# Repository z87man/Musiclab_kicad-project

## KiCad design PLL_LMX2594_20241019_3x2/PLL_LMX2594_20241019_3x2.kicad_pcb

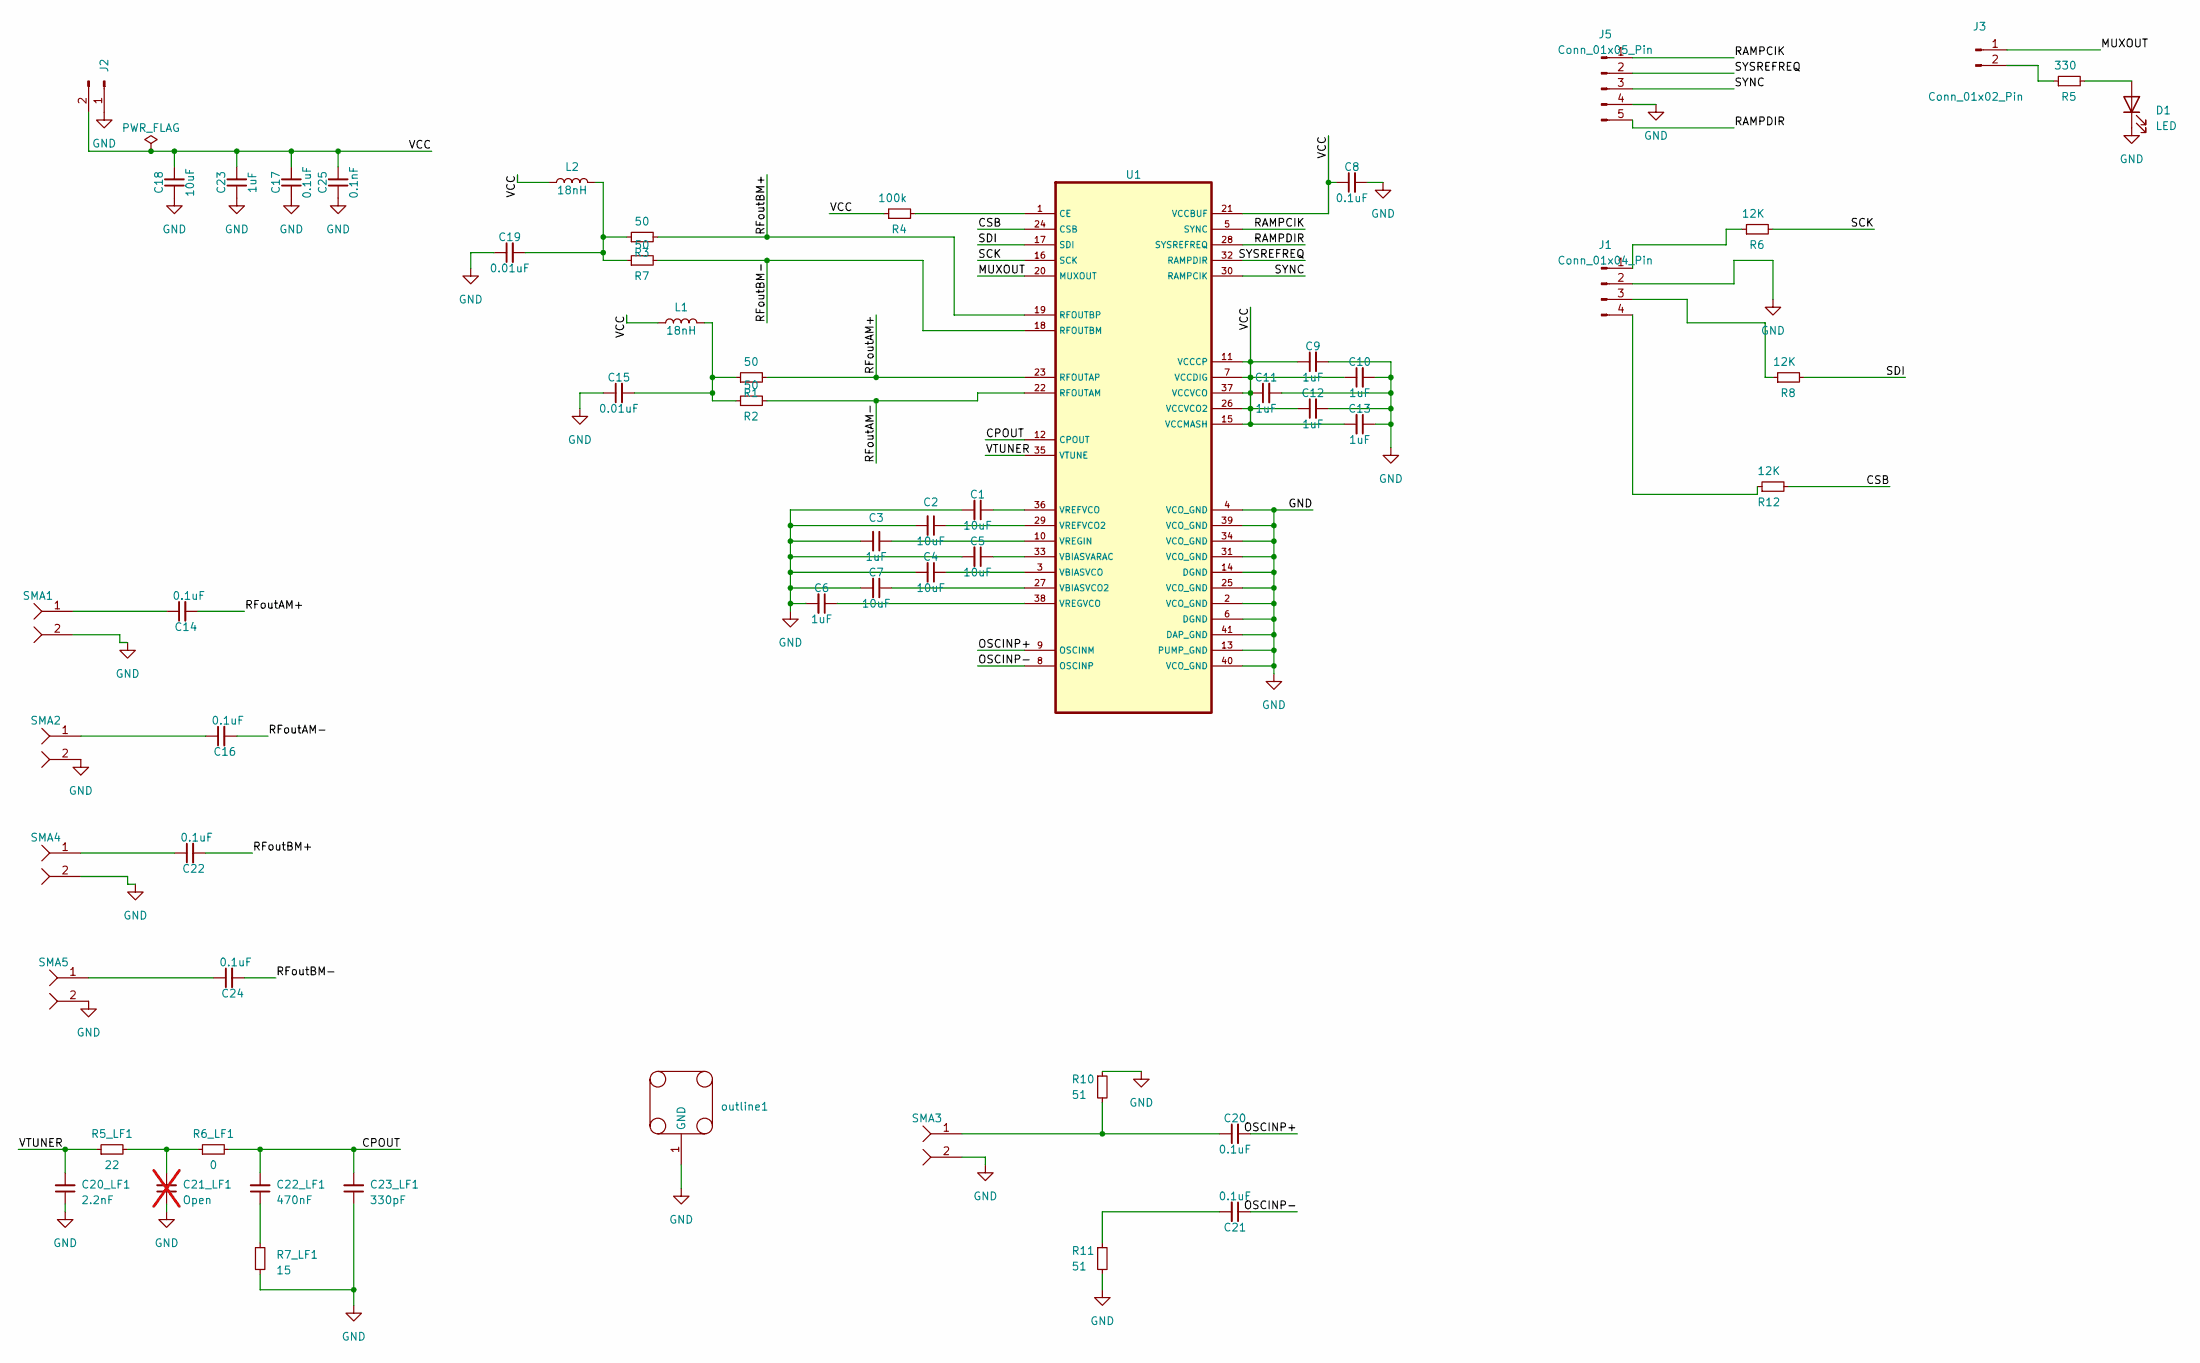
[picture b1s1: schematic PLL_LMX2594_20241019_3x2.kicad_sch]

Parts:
C1, C2, C4, C5, C7, C18: 10uF; C_0603_1608Metric
C3, C6, C9, C10, C11, C12, C13, C23: 1uF; C_0402_1005Metric
C8, C14, C16, C17, C20, C21, C22, C24: 0.1uF; C_0402_1005Metric
C15, C19: 0.01uF; C_0402_1005Metric
C20_LF1: 2.2nF; C_0402_1005Metric
C21_LF1: Open; C_0402_1005Metric; not fitted
C22_LF1: 470nF; C_0402_1005Metric
C23_LF1: 330pF; C_0402_1005Metric
C25: 0.1nF; C_0402_1005Metric
D1: LED; LED_0603_1608Metric
J1: Conn_01x04_Pin; JST_XH_B4B-XH-A_1x04_P2.50mm_Vertical
J2: Conn_01x02_Pin; JST_XH_B2B-XH-A_1x02_P2.50mm_Vertical
J3: Conn_01x02_Pin; PinHeader_1x02_P2.54mm_Vertical
J5: Conn_01x05_Pin; JST_XH_B5B-XH-A_1x05_P2.50mm_Vertical
L1, L2: 18nH; L_0603_1608Metric
R1, R2, R3, R7: 50; R_0402_1005Metric
R4: 100k; R_0402_1005Metric
R5: 330; R_0402_1005Metric
R5_LF1: 22; R_0402_1005Metric
R6, R8, R12: 12K; R_0402_1005Metric
R6_LF1: 0; R_0402_1005Metric
R7_LF1: 15; R_0402_1005Metric
R10, R11: 51; R_0402_1005Metric
SMA1, SMA2, SMA3, SMA4, SMA5: SMA_KHD_Back
U1: LMX2594-QFN41N
outline1: Outline_4x3_cavity_20230728

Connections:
/CPOUT: C22_LF1.2, C23_LF1.2, R6_LF1.2, U1.12 (CPOUT)
/MUXOUT: J3.1, U1.20 (MUXOUT)
/OSCINP+: C20.2, U1.9 (OSCINM)
/OSCINP-: C21.1, U1.8 (OSCINP)
/RAMPCIK: J5.1, U1.5 (SYNC); also elsewhere on the board
/RAMPDIR: J5.5, U1.28 (SYSREFREQ); also elsewhere on the board
/RFoutAM+: C14.2, R1.2, U1.23 (RFOUTAP)
/RFoutAM-: C16.2, R2.2, U1.22 (RFOUTAM)
/RFoutBM+: C22.2, R3.2, U1.19 (RFOUTBP)
/RFoutBM-: C24.2, R7.2, U1.18 (RFOUTBM)
/SDI: R8.2, U1.17 (SDI)
/SYNC: J5.3, U1.30 (RAMPCIK); also elsewhere on the board
/SYSREFREQ: J5.2, U1.32 (RAMPDIR); also elsewhere on the board
/VCC: C8.1, C9.1, C10.1, C11.1, C12.1, C13.2, C17.2, C18.2, C23.2, C25.2, J2.2, L1.1, L2.1, R4.1, U1.7 (VCCDIG), U1.11 (VCCCP), U1.15 (VCCMASH), U1.21 (VCCBUF), U1.26 (VCCVCO2), U1.37 (VCCVCO)
/VTUNER: C20_LF1.2, R5_LF1.1, U1.35 (VTUNE)
GND: C1.2, C2.2, C3.2, C4.2, C5.2, C6.2, C7.2, C8.2, C9.2, C10.2, C11.2, C12.2, C13.1, C15.1, C17.1, C18.1, C19.1, C20_LF1.1, C21_LF1.1, C23.1, C23_LF1.1, C25.1, D1.1 (K), J1.2, J2.1, J5.4, R7_LF1.2, R10.1, R11.2, SMA1.2, SMA2.2, SMA3.2, SMA4.2, SMA5.2, U1.2 (VCO_GND), U1.4 (VCO_GND), U1.6 (DGND), U1.13 (PUMP_GND), U1.14 (DGND), U1.25 (VCO_GND), U1.31 (VCO_GND), U1.34 (VCO_GND), U1.39 (VCO_GND), U1.40 (VCO_GND), U1.41 (DAP_GND), outline1.1 (GND); also elsewhere on the board
unnamed: C14.1, SMA1.1
unnamed: C15.2, L1.2, R1.1, R2.1
unnamed: C16.1, SMA2.1
unnamed: C19.2, L2.2, R3.1, R7.1
unnamed: C20.1, R10.2, SMA3.1
unnamed: C21.2, R11.1
unnamed: C21_LF1.2, R5_LF1.2, R6_LF1.1
unnamed: C22.1, SMA4.1
unnamed: C22_LF1.1, R7_LF1.1
unnamed: C24.1, SMA5.1
unnamed: D1.2 (A), R5.2
unnamed: J1.1, R6.1
unnamed: J1.3, R8.1
unnamed: J1.4, R12.1
unnamed: J3.2, R5.1
unnamed: R4.2, U1.1 (CE)
unnamed: C5.1, U1.33 (VBIASVARAC)
unnamed: C7.1, U1.27 (VBIASVCO2)
unnamed: C4.1, U1.3 (VBIASVCO)
unnamed: C2.1, U1.29 (VREFVCO2)
unnamed: C1.1, U1.36 (VREFVCO)
unnamed: C3.1, U1.10 (VREGIN)
unnamed: C6.1, U1.38 (VREGVCO)

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
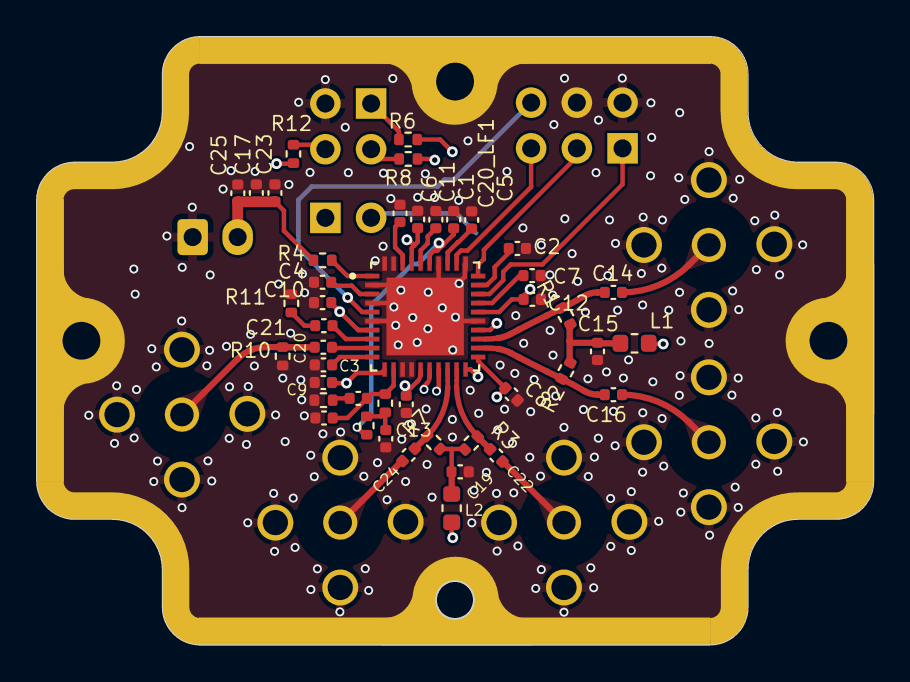
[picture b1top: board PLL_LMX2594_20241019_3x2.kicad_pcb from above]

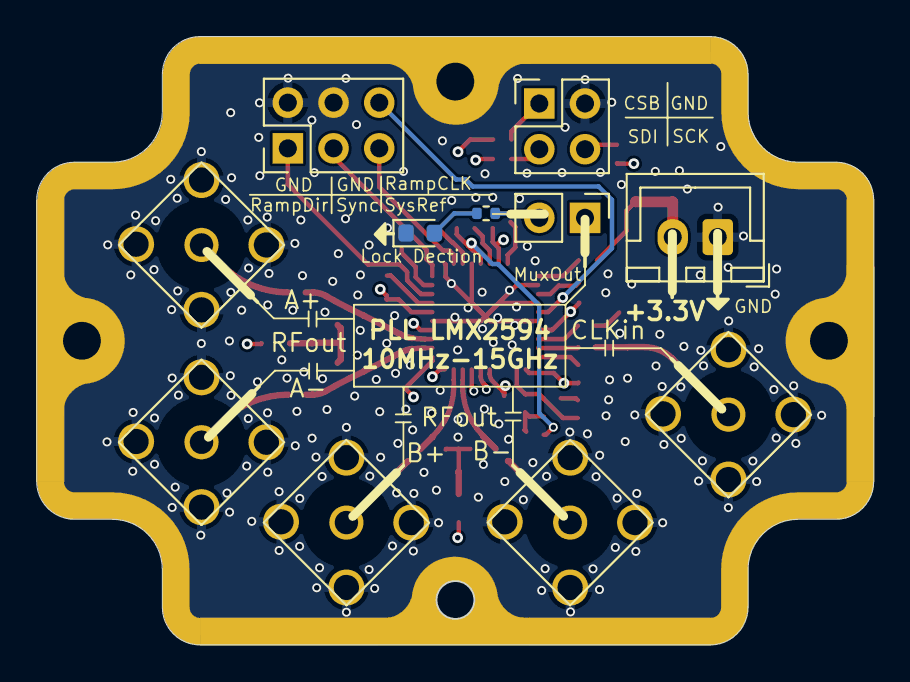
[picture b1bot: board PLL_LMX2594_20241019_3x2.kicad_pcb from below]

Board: 4 copper layers, 46.5 x 33.8 mm, 56 parts (11 on the bottom side), 41 nets.

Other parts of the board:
J4: Conn_01x06_Pin; PinHeader_2x03_P2.54mm_Vertical

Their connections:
/RAMPCIK: J4.6; also elsewhere on the board
/RAMPDIR: J4.1; also elsewhere on the board
/SYNC: J4.3; also elsewhere on the board
/SYSREFREQ: J4.5; also elsewhere on the board
GND: J4.2, J4.4; also elsewhere on the board

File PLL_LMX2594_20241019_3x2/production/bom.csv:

Designator,Footprint,Quantity,Value,LCSC Part #
"C1, C2, C4, C5, C7",0402,5,10uF,
"C10, C11, C12, C13, C23, C3, C6, C9",0402,8,1uF,
"C14, C16, C17, C20, C21, C22, C24, C8",0402,8,0.1uF,
"C15, C19",0402,2,0.01uF,
C20_LF1,0402,1,2.2nF,
C21_LF1,0402,1,Open,
C22_LF1,0402,1,470nF,
C23_LF1,0402,1,330pF,
C25,0402,1,0.1nF,
D1,0603,1,LED,
J1,PinHeader_2x02_P2.54mm_Vertical,1,Conn_01x04_Pin,
J2,JST_XH_B2B-XH-A_1x02_P2.50mm_Vertical,1,Conn_01x02_Pin,
J3,PinHeader_1x02_P2.54mm_Vertical,1,Conn_01x02_Pin,
J4,PinHeader_2x03_P2.54mm_Vertical,1,Conn_01x06_Pin,
"L1, L2",0603,2,18nH,
"R1, R2, R3, R7",0402,4,50,
"R10, R11",0402,2,51,
"R12, R6, R8",0402,3,12K,
R4,0402,1,100k,
R5,0402,1,330,
R5_LF1,0402,1,22,
R6_LF1,0402,1,0,
R7_LF1,0402,1,15,
"SMA1, SMA2, SMA3, SMA4, SMA5",SMA_KHD_Back,5,~,
U1,LMX2594-QFN41N,1,~,
outline1,Outline_3x2_cavity_1.5mm,1,~,

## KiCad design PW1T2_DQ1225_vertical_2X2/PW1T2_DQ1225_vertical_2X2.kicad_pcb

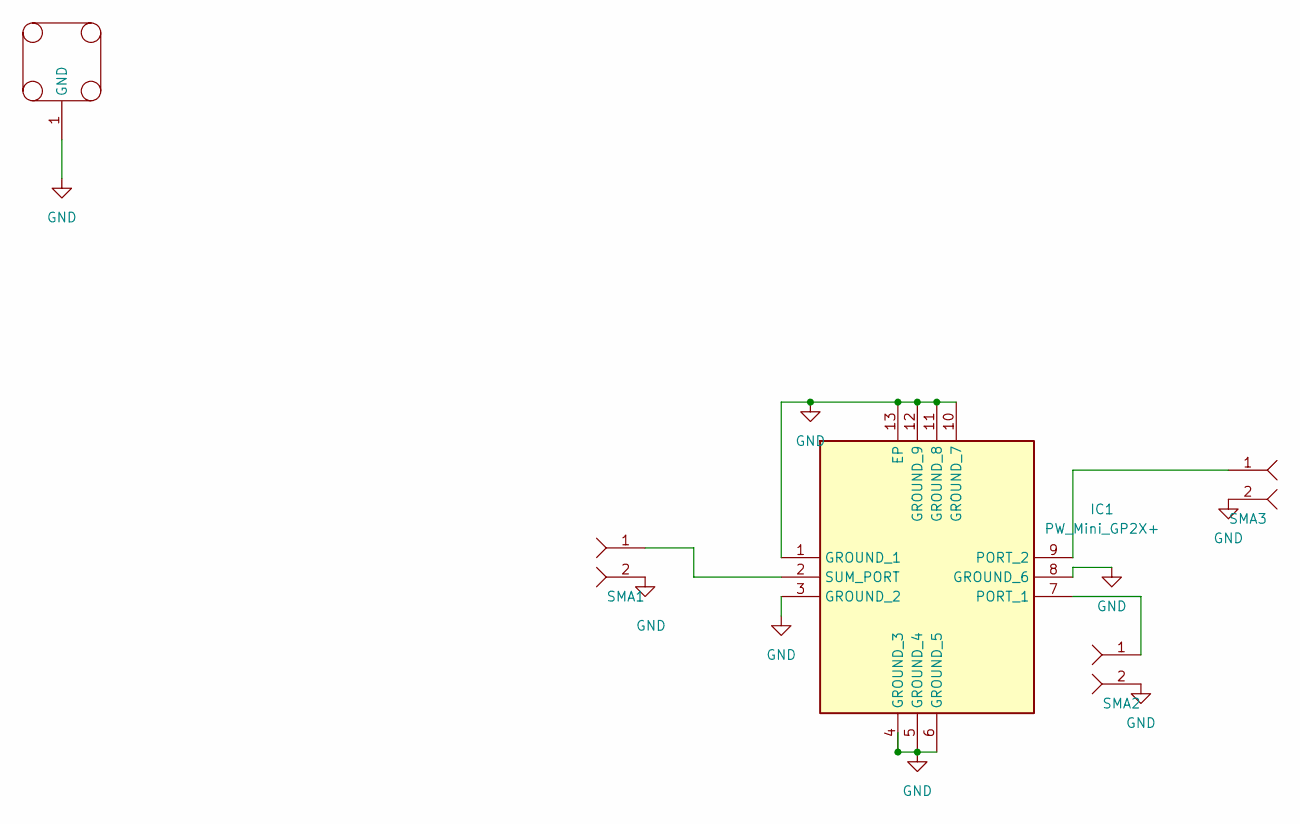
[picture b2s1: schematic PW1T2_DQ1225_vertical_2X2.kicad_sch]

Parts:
IC1: PW_Mini_GP2X+; PW_MINI_1T2_DQ1225_QFN51P300X300X89-13N; Mouser Part Number 139-GP2X
SMA1, SMA2, SMA3: SMA_KHD_Back
outline1: Outline_2x2_cavity_20231207

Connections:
GND: IC1.1 (GROUND_1), IC1.3 (GROUND_2), IC1.4 (GROUND_3), IC1.5 (GROUND_4), IC1.6 (GROUND_5), IC1.8 (GROUND_6), IC1.10 (GROUND_7), IC1.11 (GROUND_8), IC1.12 (GROUND_9), IC1.13 (EP), SMA1.2, SMA2.2, SMA3.2, outline1.1 (GND)
unnamed: IC1.7 (PORT_1), SMA2.1
unnamed: IC1.9 (PORT_2), SMA3.1
unnamed: IC1.2 (SUM_PORT), SMA1.1

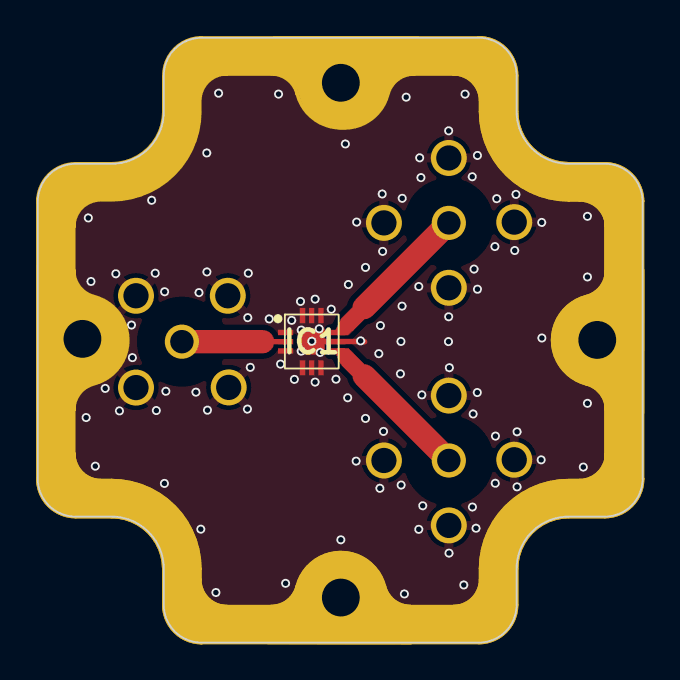
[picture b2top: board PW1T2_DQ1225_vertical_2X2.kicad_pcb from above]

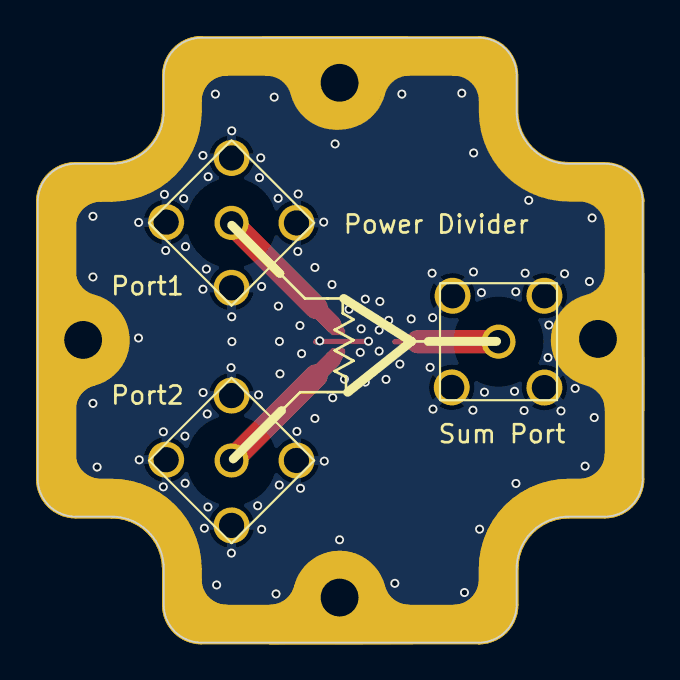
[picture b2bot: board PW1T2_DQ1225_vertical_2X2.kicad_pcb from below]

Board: 2 copper layers, 33.6 x 33.6 mm, 5 parts (3 on the bottom side), 4 nets.

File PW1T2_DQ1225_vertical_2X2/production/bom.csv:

Designator,Footprint,Quantity,Value,LCSC Part #
IC1,PW_MINI_1T2_DQ1225_QFN51P300X300X89-13N,1,PW_Mini_GP2X+,
"SMA1, SMA2, SMA3",SMA_KHD_Back,3,~,
outline1,Outline_2x2_cavity_20231207,1,~,

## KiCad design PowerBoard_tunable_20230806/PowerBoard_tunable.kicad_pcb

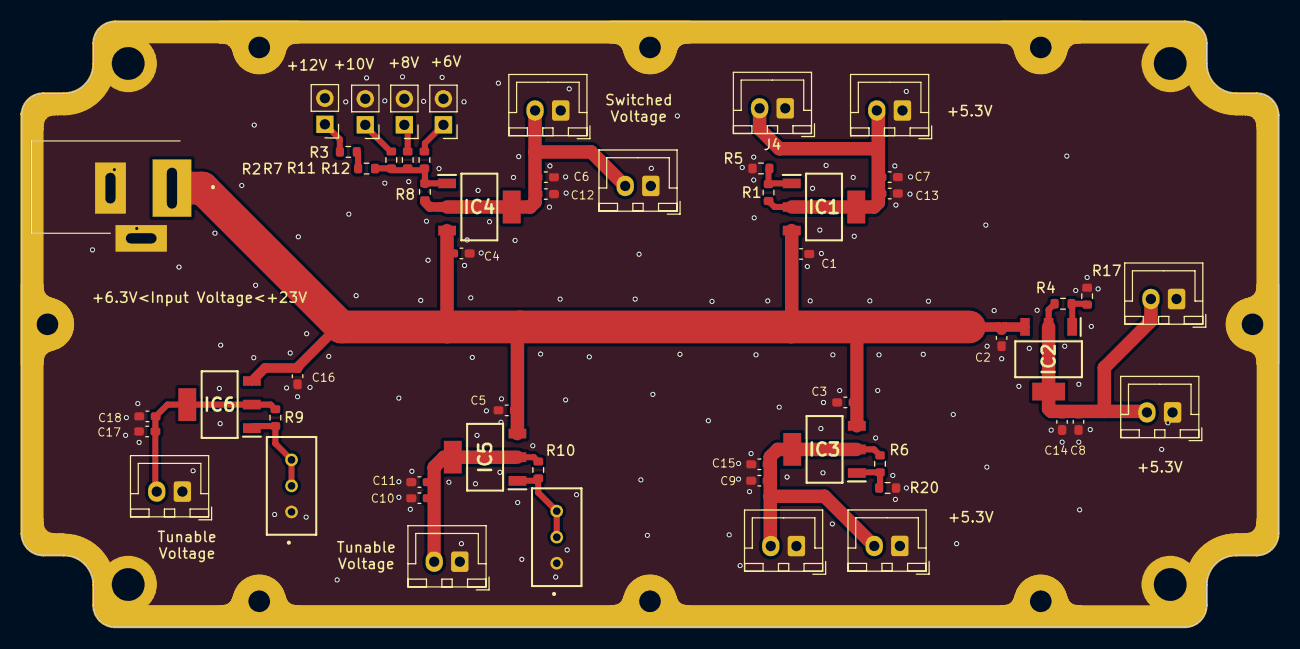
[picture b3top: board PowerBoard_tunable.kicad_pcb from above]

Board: 2 copper layers, 122.5 x 59.0 mm, 56 parts (0 on the bottom side), 19 nets.

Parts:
C1, C2, C3, C4, C5, C6, C7, C8, C9, C10, C16, C17: 0.1uF; C_0603_1608Metric_0603 usual
C11, C12, C13, C14, C15, C18: 4.7uF; C_0603_1608Metric_0603 usual
IC1, IC2, IC3, IC4, IC5, IC6: DC_LM317DCYR; DC_LM317_SOT230P700X180-4N
J1, J12, J13, J14: Conn_01x02_Pin; PinHeader_1x02_P2.54mm_Vertical
J2, J3, J4, J5, J6, J7, J8, J10, J11, J15: Conn_01x02_Pin; JST_XH_B2B-XH-A_1x02_P2.50mm_Vertical
J9: DC_Socket_4840.2211; DC_Socket_48402211
R1, R4, R6, R8, R9, R10: 1k; R_0603_1608Metric
R2, R5, R17, R20: 3.3k; R_0603_1608Metric
R3, R11: 5.6k; R_0603_1608Metric
R7: 7k; R_0603_1608Metric
R12: 3.9k; R_0603_1608Metric
VR1, VR2: Resistor_3296W-1-104LF; Resistor_3296W-1
outline1: Outline_9x4_cavity_20230711

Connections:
GND: C1.2, C2.2, C3.2, C4.2, C5.2, C6.2, C7.2, C8.2, C9.2, C10.2, C11.2, C12.2, C13.2, C14.2, C15.2, C16.2, C17.2, C18.2, J1.2, J2.1, J3.1, J4.1, J5.1, J6.1, J7.1, J8.1, J9.2, J9.3, J10.1, J11.1, J12.2, J13.2, J14.2, J15.1, R5.1, R17.1, R20.1, VR1.1 (CCW), VR2.1 (CCW), outline1.1 (GND)
unnamed: IC1.1 (ADJUST), R1.2, R5.2
unnamed: C7.1, C13.1, IC1.2 (OUTPUT_1), IC1.4 (OUTPUT_2), J2.2, J4.2, R1.1
unnamed: IC2.1 (ADJUST), R4.2, R17.2
unnamed: C8.1, C14.1, IC2.2 (OUTPUT_1), IC2.4 (OUTPUT_2), J3.2, J6.2, R4.1
unnamed: IC3.1 (ADJUST), R6.2, R20.2
unnamed: C9.1, C15.1, IC3.2 (OUTPUT_1), IC3.4 (OUTPUT_2), J5.2, J8.2, R6.1
unnamed: IC4.1 (ADJUST), R2.2, R7.2, R8.2, R11.2, R12.2
unnamed: C6.1, C12.1, IC4.2 (OUTPUT_1), IC4.4 (OUTPUT_2), J7.2, J15.2, R8.1
unnamed: IC5.1 (ADJUST), R10.2, VR1.2 (WIPER), VR1.3 (CW)
unnamed: C10.1, C11.1, IC5.2 (OUTPUT_1), IC5.4 (OUTPUT_2), J11.2, R10.1
unnamed: IC6.1 (ADJUST), R9.2, VR2.2 (WIPER), VR2.3 (CW)
unnamed: C17.1, C18.1, IC6.2 (OUTPUT_1), IC6.4 (OUTPUT_2), J10.2, R9.1
unnamed: J1.1, R3.1
unnamed: J12.1, R11.1
unnamed: J13.1, R7.1
unnamed: J14.1, R12.1
unnamed: R2.1, R3.2
input: C1.1, C2.1, C3.1, C4.1, C5.1, C16.1, IC1.3 (INPUT), IC2.3 (INPUT), IC3.3 (INPUT), IC4.3 (INPUT), IC5.3 (INPUT), IC6.3 (INPUT), J9.1

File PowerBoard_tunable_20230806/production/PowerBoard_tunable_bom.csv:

Designator,Footprint,Quantity,Value,LCSC Part #
"C1, C10, C16, C17, C2, C3, C4, C5, C6, C7, C8, C9",0603,12,0.1uF,
"C11, C12, C13, C14, C15, C18",0603,6,4.7uF,
"IC1, IC2, IC3, IC4, IC5, IC6",DC_LM317_SOT230P700X180-4N,6,DC_LM317DCYR,
"J1, J12, J13, J14",PinHeader_1x02_P2.54mm_Vertical,4,Conn_01x02_Pin,
"J10, J11, J15, J2, J3, J4, J5, J6, J7, J8",JST_XH_B2B-XH-A_1x02_P2.50mm_Vertical,10,Conn_01x02_Pin,
J9,DC_Socket_48402211,1,DC_Socket_4840.2211,
"R1, R10, R4, R6, R8, R9",0603,6,1k,
"R11, R3",0603,2,5.6k,
R12,0603,1,3.9k,
"R17, R2, R20, R5",0603,4,3.3k,
R7,0603,1,7k,
"VR1, VR2",Resistor_3296W-1,2,Resistor_3296W-1-104LF,
outline1,Outline_9x4_cavity_20230711,1,~,

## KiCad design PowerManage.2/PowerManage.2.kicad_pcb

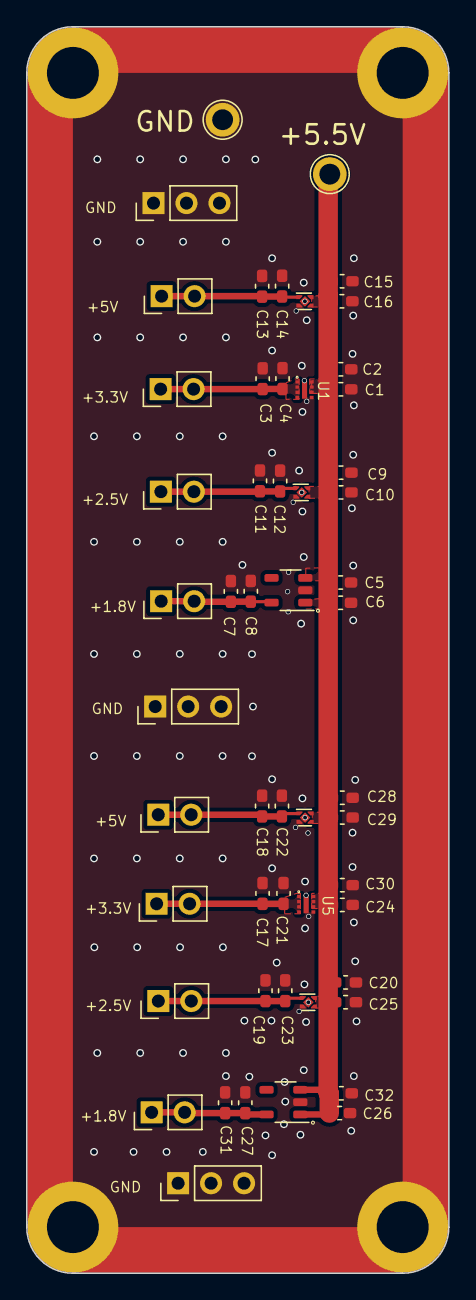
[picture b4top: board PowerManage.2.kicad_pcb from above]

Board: 2 copper layers, 32.5 x 96.0 mm, 54 parts (0 on the bottom side), 10 nets.

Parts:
C1, C3, C5, C7, C9, C11, C13, C15, C18, C19, C21, C24, C25, C26, C28, C31: 0.1uF; 0603 usual
C2, C4, C6, C8, C10, C12, C14, C16, C17, C20, C22, C23, C27, C29, C30, C32: 1uf; 0603 usual
J1, J2, J3, J4, J5, J6, J12, J13: Conn_01x02_Pin; PinHeader_1x02_P2.54mm_Vertical
J7, J8, J9: Conn_01x03_Pin; PinHeader_1x03_P2.54mm_Vertical
TP1, TP2: TestPoint; TestPoint_Plated_Hole_D1.6mm
TP3: TestPoint; Outline_7x2
U1, U5: LD56100DPU30R; DFN-8_1.2x1.6mm
U2, U6: TPS7A2018PDBVR; SOT_23_1.45mm
U3, U8: TPS7A2025PDQNR; Texas_X2SON-4_1x1mm_P0.65mm
U4, U7: TPS7A2050PDQNR; Texas_X2SON-4_1x1mm_P0.65mm

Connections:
/+1.8V_1: C7.1, C8.1, J4.1, J4.2, U2.5 (OUT)
/+1.8V_2: C27.1, C31.1, J12.1, J12.2, U6.5 (OUT)
/+2.5V_1: C11.1, C12.1, J5.1, J5.2, U3.1 (OUT)
/+2.5V_2: C19.1, C23.1, J2.1, J2.2, U8.1 (OUT)
/+3.3V_1: C3.1, C4.1, J3.1, J3.2, U1.1 (VOUT), U1.2 (VOUT), U1.3 (LCON), U1.4 (FB)
/+3.3V_2: C17.1, C21.1, J13.1, J13.2, U5.1 (VOUT), U5.2 (VOUT), U5.3 (LCON), U5.4 (FB)
/+5V_1: C13.1, C14.1, J6.1, J6.2, U4.1 (OUT)
/+5V_2: C18.1, C22.1, J1.1, J1.2, U7.1 (OUT)
GND: C1.2, C2.2, C3.2, C4.2, C5.2, C6.2, C7.2, C8.2, C9.2, C10.2, C11.2, C12.2, C13.2, C14.2, C15.2, C16.2, C17.2, C18.2, C19.2, C20.2, C21.2, C22.2, C23.2, C24.2, C25.2, C26.2, C27.2, C28.2, C29.2, C30.2, C31.2, C32.2, J7.1, J7.2, J7.3, J8.1, J8.2, J8.3, J9.1, J9.2, J9.3, TP2.1, TP3.1, U1.5 (GND), U1.9 (GND), U2.2 (GND), U3.2 (GND), U3.5 (GND), U4.2 (GND), U4.5 (GND), U5.5 (GND), U5.9 (GND), U6.2 (GND), U7.2 (GND), U7.5 (GND), U8.2 (GND), U8.5 (GND)
VDD: C1.1, C2.1, C5.1, C6.1, C9.1, C10.1, C15.1, C16.1, C20.1, C24.1, C25.1, C26.1, C28.1, C29.1, C30.1, C32.1, TP1.1, U1.6 (EN), U1.7 (IN), U1.8 (IN), U2.1 (IN), U2.3 (EN), U3.3 (EN), U3.4 (IN), U4.3 (EN), U4.4 (IN), U5.6 (EN), U5.7 (IN), U5.8 (IN), U6.1 (IN), U6.3 (EN), U7.3 (EN), U7.4 (IN), U8.3 (EN), U8.4 (IN)

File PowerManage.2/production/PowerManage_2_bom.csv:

Designator,Footprint,Quantity,Value,LCSC Part #
"C1, C11, C13, C15, C18, C19, C21, C24, C25, C26, C28, C3, C31, C5, C7, C9",0603 usual,16,0.1uF,
"C10, C12, C14, C16, C17, C2, C20, C22, C23, C27, C29, C30, C32, C4, C6, C8",0603 usual,16,1uf,
"J1, J12, J13, J2, J3, J4, J5, J6",PinHeader_1x02_P2.54mm_Vertical,8,Conn_01x02_Pin,
"J10, J11, J7, J8, J9",PinHeader_1x03_P2.00mm_Vertical,5,Conn_01x03_Pin,
"TP1, TP2",TestPoint_2mmdll,2,TestPoint,
TP3,101.6x38.1,1,TestPoint,
"U1, U5",DFN-8_1.2x1.6mm,2,LD56100DPU30R,
"U2, U6",SOT_23_1.45mm,2,TPS7A2018PDBVR,
"U3, U8",Texas_X2SON-4_1x1mm_P0.65mm,2,TPS7A2025PDQNR,
"U4, U7",Texas_X2SON-4_1x1mm_P0.65mm,2,TPS7A2050PDQNR,

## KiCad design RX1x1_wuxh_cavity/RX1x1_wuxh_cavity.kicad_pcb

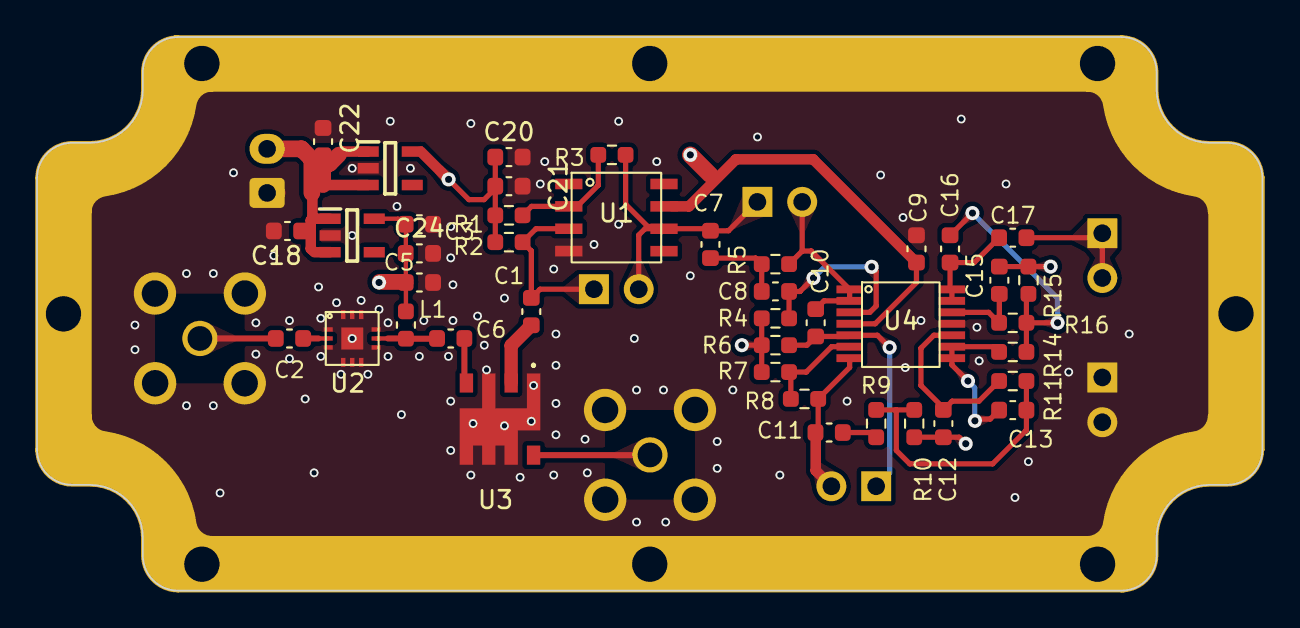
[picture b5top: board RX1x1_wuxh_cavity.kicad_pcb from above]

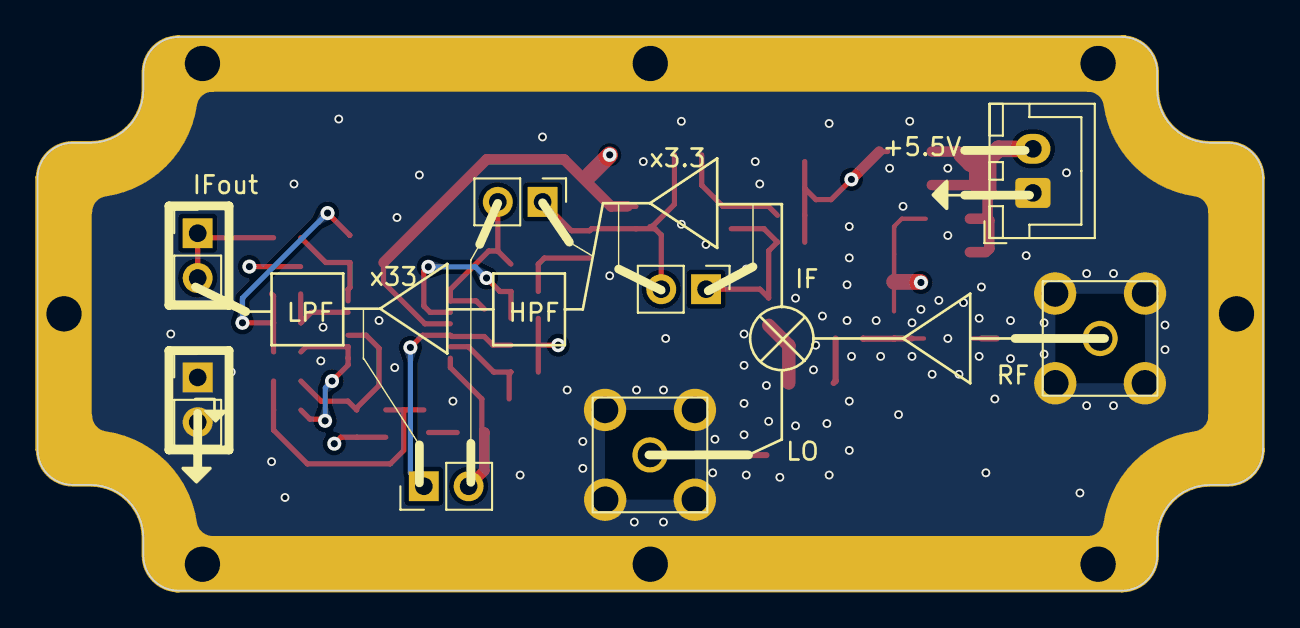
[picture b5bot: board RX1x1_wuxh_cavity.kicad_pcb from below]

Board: 4 copper layers, 69.5 x 31.4 mm, 50 parts (8 on the bottom side), 27 nets.

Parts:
C1, C10, C11, C17: 1u; C_0603_1608Metric_revised
C2, C6: 22 uF; C_0603_1608Metric_revised
C3: 4.7 uF; C_0603_1608Metric_revised
C5: 1 nF; C_0603_1608Metric_revised
C7: 200p; C_0603_1608Metric_revised
C8: 110p; C_0603_1608Metric_revised
C9: 2.2u; C_0603_1608Metric_revised
C12, C15: 100p; C_0603_1608Metric_revised
C13: 120p; C_0603_1608Metric_revised
C16: 750p; C_0603_1608Metric_revised
C18, C20, C22, C24: 1uf; C_0603_1608Metric_revised
C21: 4.7uF; C_0603_1608Metric_revised
IC1: TPS7A2025PDBVR; DC_SOT95P280X145-5N
IC2: TPS7A2050PDBVR; DC_SOT95P280X145-5N
J1, J2, J3: Conn_01x02; PinHeader_1x02_P2.54mm_Vertical
J4: Conn_01x02_Pin; JST_XH_B2B-XH-A_1x02_P2.50mm_Vertical
J6, J7: Conn_01x02_Pin; PinHeader_1x02_P2.54mm_Vertical
L1: 15 nH; L_0603_1608Metric_revised
R1, R2, R6, R7: 1k; R_0603_1608Metric_revised
R3: 3.3k; R_0603_1608Metric_revised
R4: 16k; R_0603_1608Metric_revised
R5: 7.5k; R_0603_1608Metric_revised
R8: 33k; R_0603_1608Metric_revised
R9: 6.2k; R_0603_1608Metric_revised
R10, R15: 100k; R_0603_1608Metric_revised
R11: 8.2k; R_0603_1608Metric_revised
R14: 2.2k; R_0603_1608Metric_revised
R16: 3.9k; R_0603_1608Metric_revised
SMA1, SMA2: SMA_KHD
U1: OPA1611_SOIC8; OPA1611-SOIC8
U2: PMA-63GLN+; PMA3-63GLN+
U3: SIM73L
U4: TL974IPWR
outline1: Outline_5x2_cavity_20230711

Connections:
+2.5V: C12.2, C15.2, C20.1, C21.1, IC1.5 (OUT), R1.2, R2.2, R4.1, R6.2, R7.2, R10.2, R15.2
+5V: C3.1, C5.1, C9.1, C24.1, IC2.5 (OUT), L1.1, U1.7 (V+), U4.4 (V+)
/RX_singleChannel/IF: C1.1, U3.2 (IF)
GND: C3.2, C5.2, C9.2, C18.2, C20.2, C21.2, C22.2, C24.2, IC1.2 (GND), IC2.2 (GND), J4.1, J7.1, J7.2, SMA1.2, SMA2.2, U1.4 (V-), U2.1 (NC), U2.3 (NC), U2.4 (NC), U2.5 (NC), U2.6 (NC), U2.7 (NC), U2.9 (NC), U2.10 (NC), U2.11 (NC), U2.12 (NC), U2.13 (EP), U3.1 (GND), U3.3 (GND), U3.5 (GND), U3.6 (GND), U3.7 (GND), U3.9 (GND), U4.11 (V-), outline1.1 (GND)
unnamed: C2.1, SMA1.1
unnamed: C7.2, C8.1, R5.1
unnamed: C11.2, R9.1
unnamed: C12.1, R11.2, U4.10 (In)
unnamed: C13.1, R9.2, R10.1, R11.1
unnamed: C15.1, R16.2, U4.12 (In)
unnamed: C16.1, R14.2, R15.1, R16.1
unnamed: C1.2, J1.1, R2.1, U1.3 (in+)
unnamed: C7.1, J1.2, J2.1, R3.2, U1.6 (Out)
unnamed: C10.1, J2.2, R5.2, U4.1 (Out), U4.2 (in-)
unnamed: C10.2, J3.1, R6.1, U4.5 (In)
unnamed: C11.1, J3.2, R8.2, U4.7 (Out)
unnamed: C17.2, J6.1, J6.2
unnamed: R7.1, R8.1, U4.6 (In)
unnamed: R1.1, R3.1, U1.2 (in-)
unnamed: C2.2, U2.2 (RFin)
unnamed: C6.1, L1.2, U2.8 (RFout&DCin)
unnamed: SMA2.1, U3.8 (LO)
unnamed: C6.2, U3.4 (RF)
unnamed: C8.2, R4.2, U4.3 (in+)
unnamed: C13.2, R14.1, U4.8 (Out), U4.9 (In)
unnamed: C16.2, C17.1, U4.13 (In), U4.14 (Out)
Vin: C18.1, C22.1, IC1.1 (IN), IC1.3 (EN), IC2.1 (IN), IC2.3 (EN), J4.2
